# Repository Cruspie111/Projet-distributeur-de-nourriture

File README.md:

# Projet-distributeur-de-nourriture
Développer un distributeur de nourriture pour mon animal de compagnie

Ce projet consiste à développer un distributeur de nourriture pour mon animal de compagnie afin de faciliter sa nourriture pendant que je suis absent pour aller à l'école. 
Il se compose de deux parties principales : 
  - La conception de la carte électronique à l'aide du logiciel Kicad
  - La programmation de la microcontrôleur Arduino Nano à l'aide du logiciel Arduino.

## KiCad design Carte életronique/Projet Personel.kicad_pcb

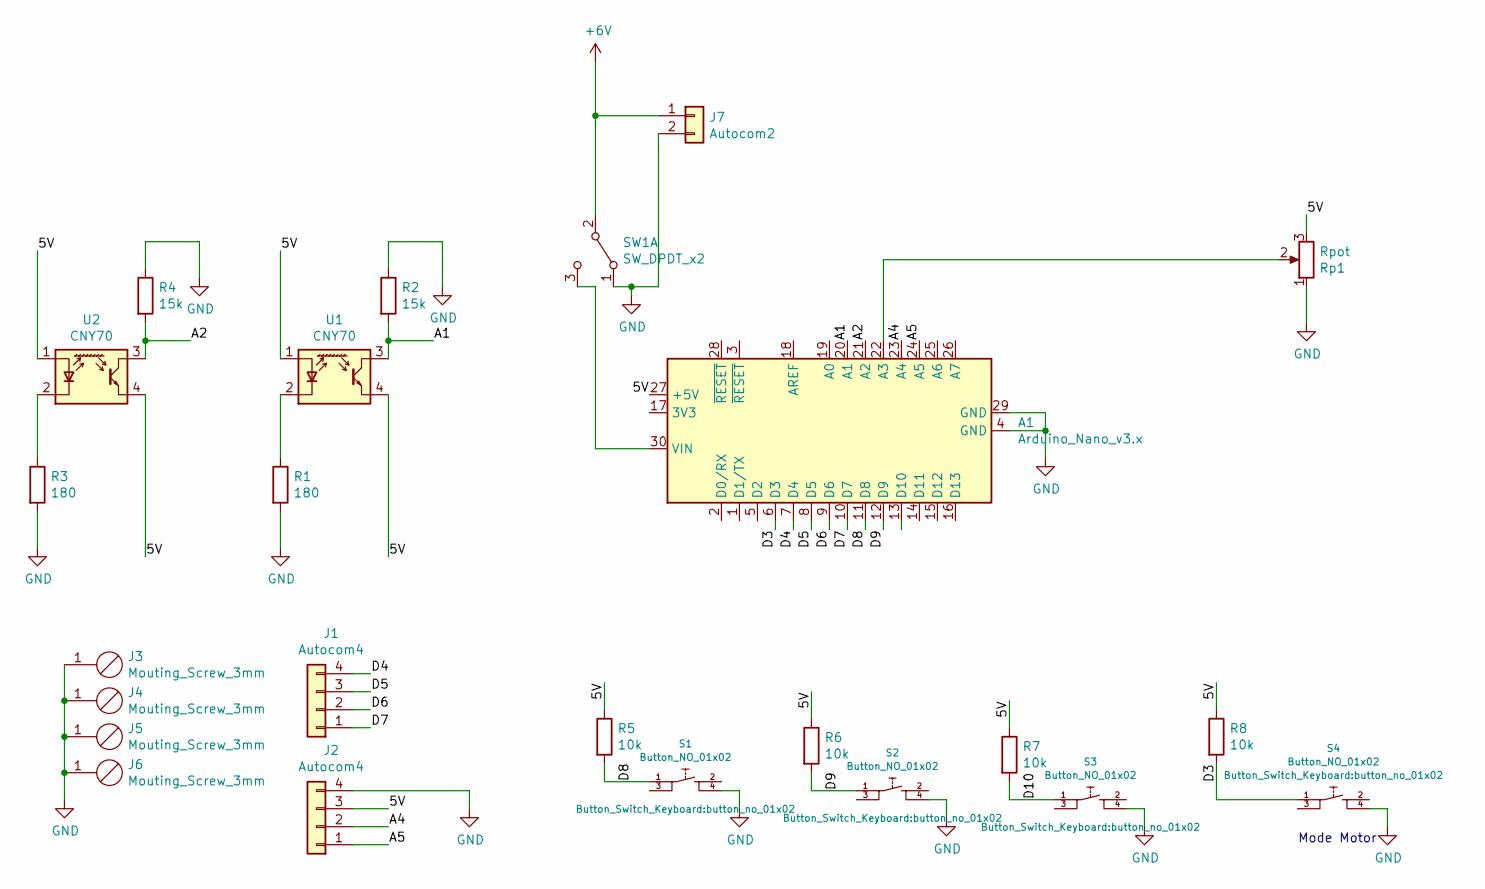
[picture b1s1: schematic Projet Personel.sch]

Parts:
A1: Arduino_Nano_v3.x; Arduino_Nano
J1, J2: Autocom4
J3, J4, J5, J6: Mouting_Screw_3mm
J7: Autocom2
R1, R3: 180; R_Axial_DIN0207_L6.3mm_D2.5mm_P10.16mm_Horizontal
R2, R4: 15k; R_Axial_DIN0207_L6.3mm_D2.5mm_P10.16mm_Horizontal
R5, R6, R7, R8: 10k; R_Axial_DIN0207_L6.3mm_D2.5mm_P10.16mm_Horizontal
Rp1: Rpot; Potentiometer_ACP_CA9-V10_Vertical
S1, S2, S3, S4: Button_NO_01x02; button_no_01x02
SW1: SW_DPDT_x2; SW_MINI-SPDT-SW
U1, U2: CNY70; Vishay_CNY70

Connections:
+6V: J7.1, SW1.2 (B)
/5V: A1.27 (+5V), J2.3, R5.1, R6.1, R7.1, R8.1, Rp1.3, U1.1 (A), U1.4 (E), U2.1 (A), U2.4 (E)
/A1: A1.20 (A1), R2.2, U1.3 (C)
/A2: A1.21 (A2), R4.2, U2.3 (C)
/A4: A1.23 (A4), J2.2
/A5: A1.24 (A5), J2.1
/D4: A1.7 (D4), J1.4
/D5: A1.8 (D5), J1.3
/D6: A1.9 (D6), J1.2
/D7: A1.10 (D7), J1.1
/D8: A1.11 (D8), R5.2, S1.1
/D9: A1.12 (D9), R6.2, S2.1
/D10: A1.13 (D10), R7.2, S3.1
GND: A1.4 (GND), A1.29 (GND), J2.4, J3.1, J4.1, J5.1, J6.1, J7.2, R1.2, R2.1, R3.2, R4.1, Rp1.1, S1.4, S2.4, S3.4, S4.4, SW1.1 (A)
unnamed: A1.6 (D3), R8.2, S4.1
unnamed: A1.22 (A3), Rp1.2
unnamed: A1.30 (VIN), SW1.3 (C)
unnamed: R1.1, U1.2 (K)
unnamed: R3.1, U2.2 (K)

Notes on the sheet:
Mode Motor

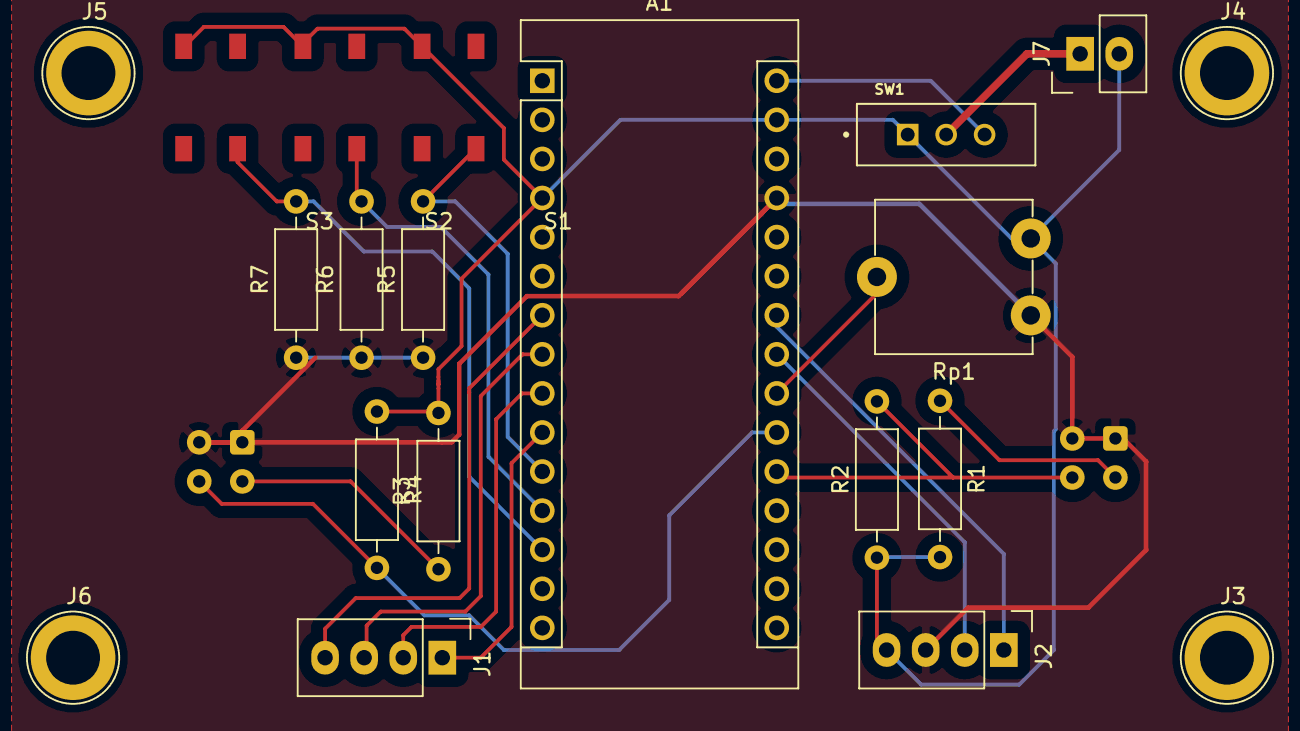
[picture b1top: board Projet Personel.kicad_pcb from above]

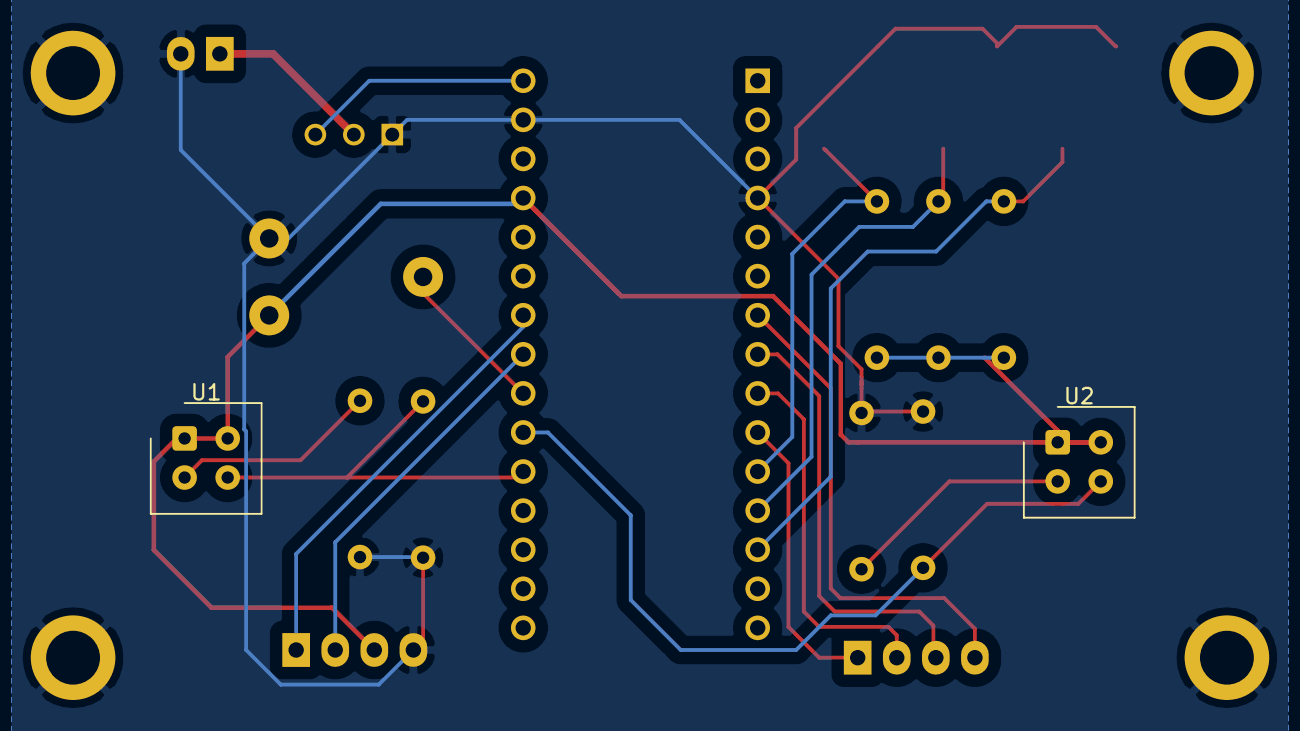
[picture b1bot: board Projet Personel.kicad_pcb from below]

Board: 2 copper layers, 22 parts (2 on the bottom side), 18 nets.

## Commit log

2023-04-28 Add files via upload
    Machine code
